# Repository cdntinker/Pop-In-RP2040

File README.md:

Slowly developing a standardised module design

# Pop-In RP2040

First in a potential series...

VERY MUCH a WIP!

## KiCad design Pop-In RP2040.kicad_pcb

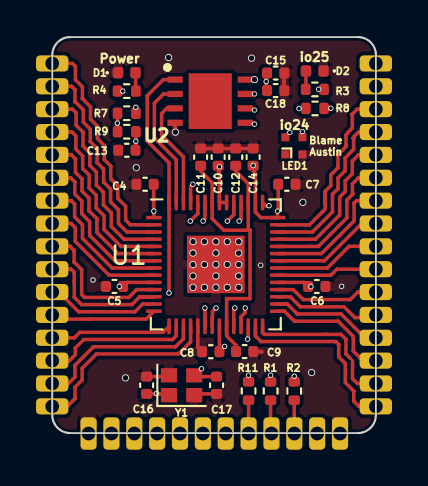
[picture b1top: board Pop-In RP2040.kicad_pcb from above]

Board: 4 copper layers, 18.0 x 22.0 mm, 29 parts (0 on the bottom side), 20 nets.

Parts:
C4, C5, C6, C7, C8, C9, C10, C11, C15: 100n; C_0402_1005Metric
C12, C13, C14, C18: 2u2; C_0402_1005Metric
C16, C17: 20p; C_0402_1005Metric
D1, D2: LED; LED_0402_1005Metric
LED1: XL-1010RGBC-WS2812B; XL1010RGBCWS2812B
R1, R2: 27; R_0402_1005Metric
R3: 470; R_0402_1005Metric
R4: 2k2; R_0402_1005Metric
R7: 200; R_0402_1005Metric
R8: ???; R_0402_1005Metric
R9: 1; R_0402_1005Metric
R11: 1k; R_0402_1005Metric
U1: RP2040; QFN-56-1EP_7x7mm_P0.4mm_EP3.2x3.2mm
U2: W25Q32JVXGIQ; SON80P400X400X50-9N
Y1: 12MHz; Crystal_SMD_2016-4Pin_2.0x1.6mm

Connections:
+1V1: C9.1, C11.1, C12.2, U1.23 (DVDD), U1.45 (VREG_VOUT), U1.50 (DVDD)
+3V3: C4.1, C5.1, C6.1, C7.1, C8.1, C10.1, C14.1, C15.1, C18.2, R4.1, R7.2, R8.1, U1.1 (IOVDD), U1.10 (IOVDD), U1.22 (IOVDD), U1.33 (IOVDD), U1.42 (IOVDD), U1.44 (VREG_IN), U1.48 (USB_VDD), U1.49 (IOVDD), U2.8 (VCC)
ADC_REF: R7.1, R9.2
GND: C4.2, C5.2, C6.2, C7.2, C8.2, C9.2, C10.2, C11.2, C12.1, C13.1, C14.2, C15.2, C16.2, C17.2, C18.1, D1.1 (K), D2.1 (K), LED1.3 (GND), U1.19 (TESTEN), U1.57 (GND), U2.4 (GND), Y1.2, Y1.4
unnamed: C13.2, R9.1, U1.43 (ADC_AVDD)
unnamed: C16.1, U1.20 (XIN), Y1.1
unnamed: C17.1, U1.21 (XOUT), Y1.3
unnamed: D1.2 (A), R4.2
unnamed: D2.2 (A), R3.2
unnamed: LED1.2 (VDD), R8.2
unnamed: R1.2, U1.47 (USB_DP)
unnamed: R2.2, U1.46 (USB_DM)
QSPI SS: R11.1, U1.56 (QSPI_SS), U2.1 (~CS)
QSPI_SCLK: U1.52 (QSPI_SCLK), U2.6 (CLK)
QSPI_SD0: U1.53 (QSPI_SD0), U2.5 (DI(IO0))
QSPI_SD1: U1.55 (QSPI_SD1), U2.2 (DO(IO1))
QSPI_SD2: U1.54 (QSPI_SD2), U2.3 (IO2)
QSPI_SD3: U1.51 (QSPI_SD3), U2.7 (IO3)
io24: LED1.4 (DI), U1.36 (GPIO24)
io25: R3.1, U1.37 (GPIO25)

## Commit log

2023-07-09 fixin the TEST footprint
2023-07-10 Seriously messin' with 3D
2023-07-10 added some renders
2023-07-10 Moar 3D fiddlin'
